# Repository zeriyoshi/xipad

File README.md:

# Xipad
T^3 The Teihen Tastatur Keyboard.
Gaming Macropad for Xipher.

## changelog
**rev1**
- fix typo (xiphad -> xipad)
- remove front-side silk prints.
- add center mount-hole.

**rev0**
- initial release.

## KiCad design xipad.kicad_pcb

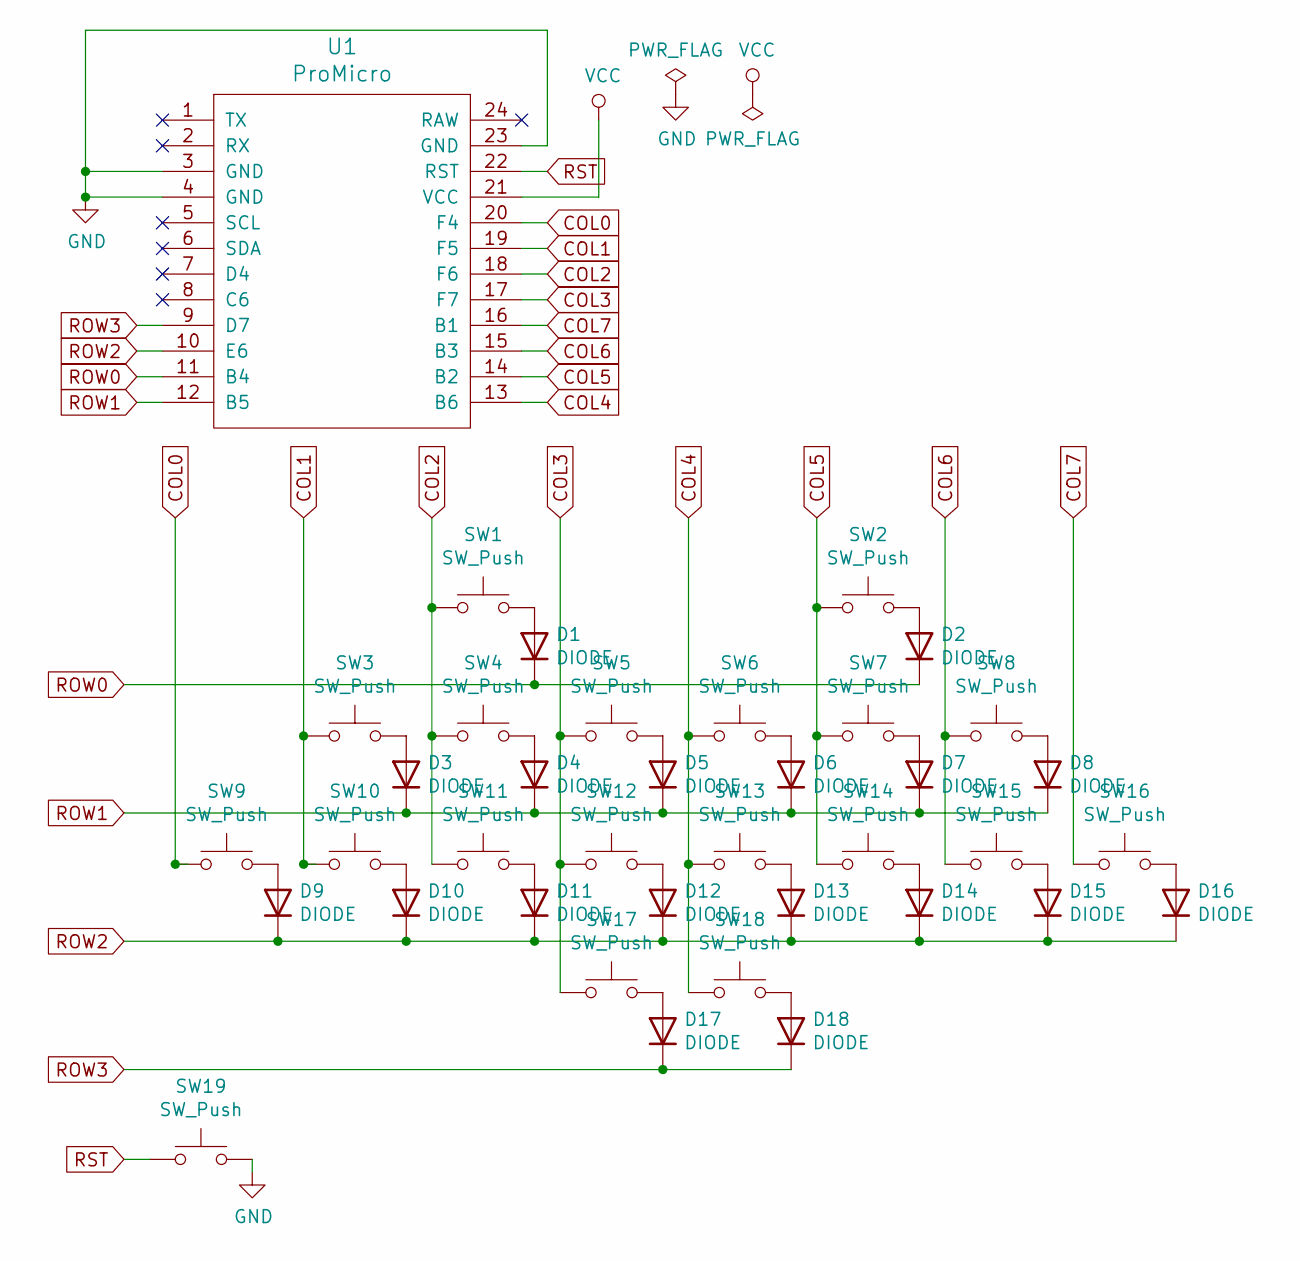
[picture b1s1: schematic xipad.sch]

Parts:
D1, D2, D3, D4, D5, D6, D7, D8, D9, D10, D11, D12, D13, D14, D15, D16, D17, D18: DIODE; Diode-dual
SW1, SW2, SW3, SW4, SW5, SW6, SW7, SW8, SW10, SW11, SW12, SW13, SW14, SW15: SW_Push; CherryMX_Choc_1u
SW9, SW16, SW17, SW18: SW_Push; CherryMX_Choc_1.5u
SW19: SW_Push; ResetSW
U1: ProMicro; ArduinoProMicro-ZigZag

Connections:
COL0: SW9.1, U1.20 (F4)
COL1: SW3.1, SW10.1, U1.19 (F5)
COL2: SW1.1, SW4.1, SW11.1, U1.18 (F6)
COL3: SW5.1, SW12.1, SW17.1, U1.17 (F7)
COL4: SW6.1, SW13.1, SW18.1, U1.13 (B6)
COL5: SW2.1, SW7.1, SW14.1, U1.14 (B2)
COL6: SW8.1, SW15.1, U1.15 (B3)
COL7: SW16.1, U1.16 (B1)
GND: SW19.2, U1.3 (GND), U1.4 (GND), U1.23 (GND)
unnamed: D1.1 (A), SW1.2
unnamed: D2.1 (A), SW2.2
unnamed: D3.1 (A), SW3.2
unnamed: D4.1 (A), SW4.2
unnamed: D5.1 (A), SW5.2
unnamed: D6.1 (A), SW6.2
unnamed: D7.1 (A), SW7.2
unnamed: D8.1 (A), SW8.2
unnamed: D9.1 (A), SW9.2
unnamed: D10.1 (A), SW10.2
unnamed: D11.1 (A), SW11.2
unnamed: D12.1 (A), SW12.2
unnamed: D13.1 (A), SW13.2
unnamed: D14.1 (A), SW14.2
unnamed: D15.1 (A), SW15.2
unnamed: D16.1 (A), SW16.2
unnamed: D17.1 (A), SW17.2
unnamed: D18.1 (A), SW18.2
ROW0: D1.2 (K), D2.2 (K), U1.11 (B4)
ROW1: D3.2 (K), D4.2 (K), D5.2 (K), D6.2 (K), D7.2 (K), D8.2 (K), U1.12 (B5)
ROW2: D9.2 (K), D10.2 (K), D11.2 (K), D12.2 (K), D13.2 (K), D14.2 (K), D15.2 (K), D16.2 (K), U1.10 (E6)
ROW3: D17.2 (K), D18.2 (K), U1.9 (D7)
RST: SW19.1, U1.22 (RST)

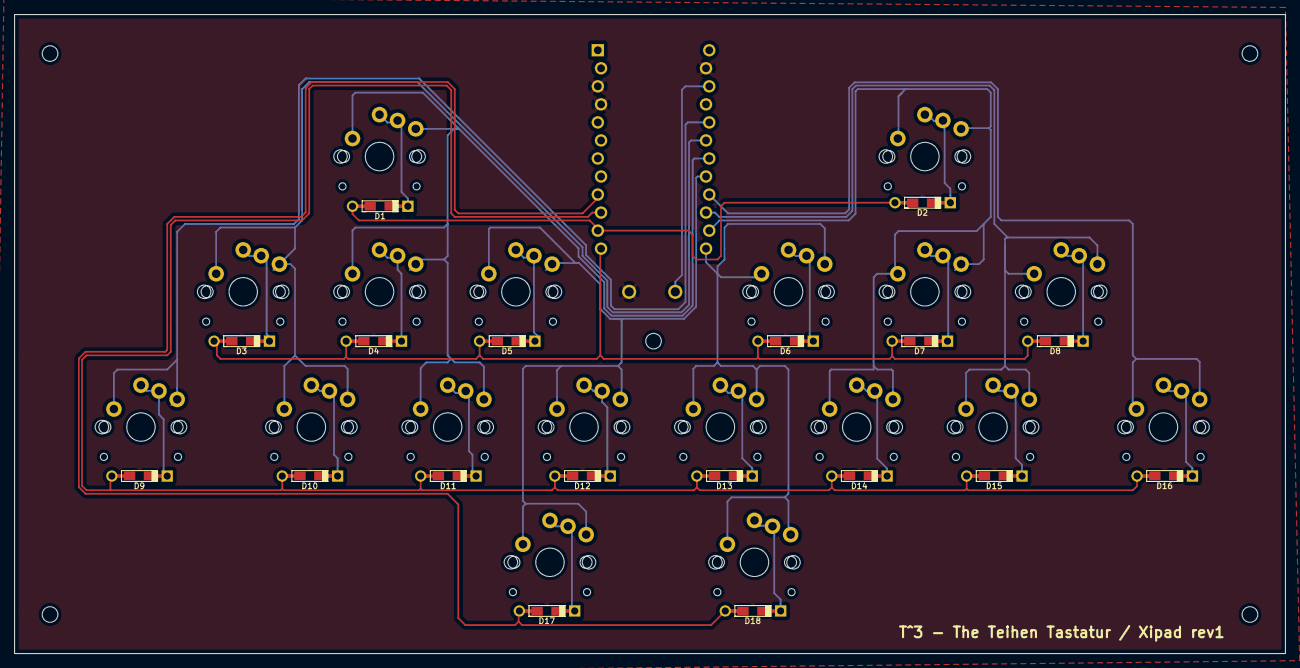
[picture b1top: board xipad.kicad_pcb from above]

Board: 2 copper layers, 179.0 x 90.0 mm, 38 parts (0 on the bottom side), 32 nets.

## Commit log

2020-06-20 initial commit.
2020-07-03 revision 1 (remove frontside silk, add center mounting hole.)
